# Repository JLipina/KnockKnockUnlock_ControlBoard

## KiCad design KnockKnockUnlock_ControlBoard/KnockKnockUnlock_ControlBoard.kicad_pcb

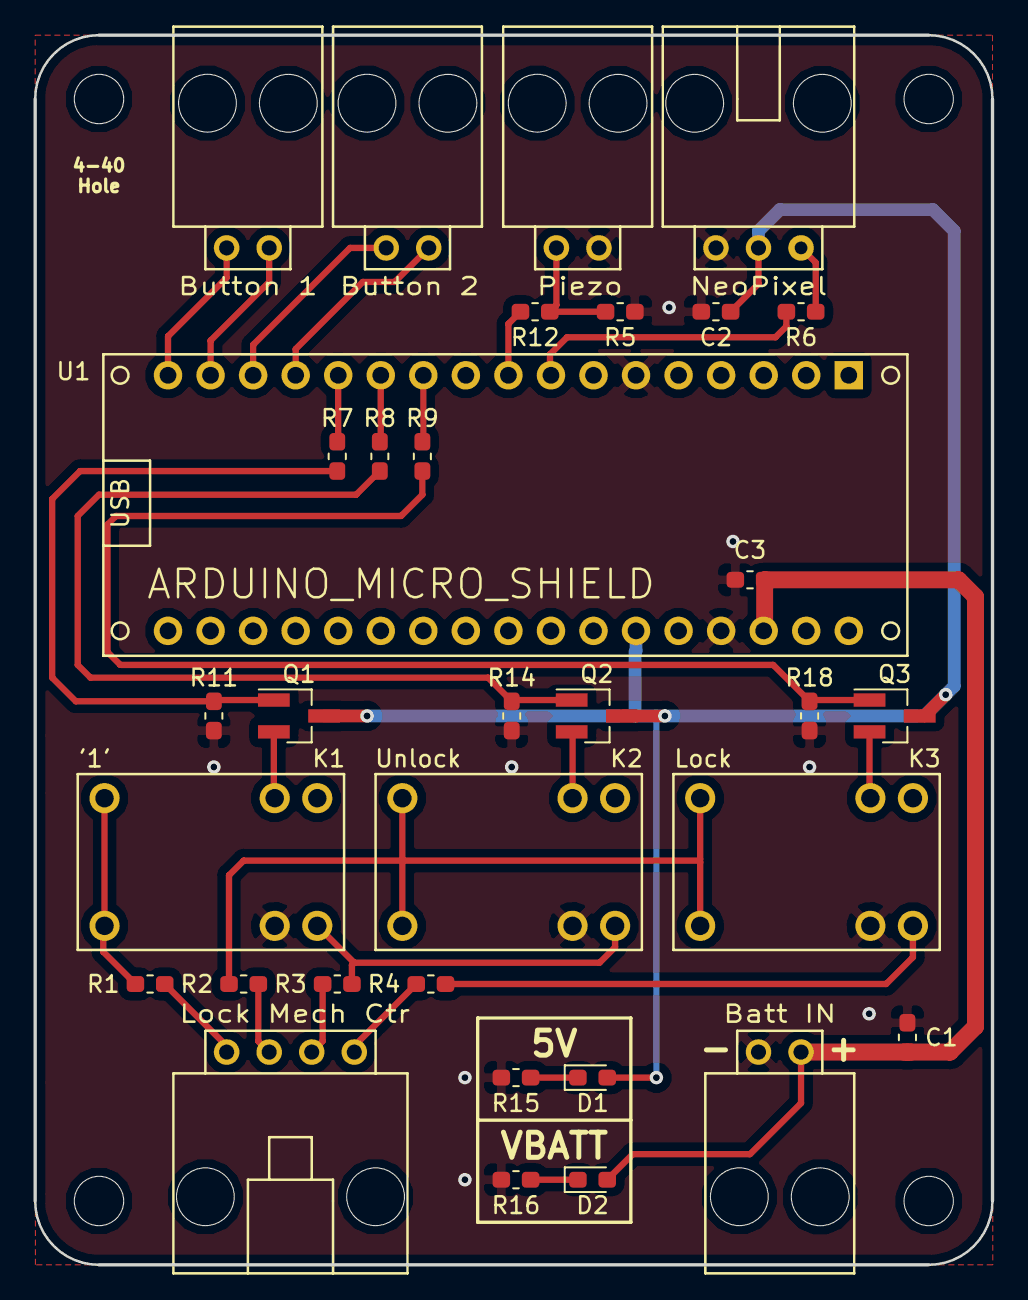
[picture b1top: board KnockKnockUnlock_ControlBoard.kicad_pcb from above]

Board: 2 copper layers, 57.2 x 73.4 mm, 33 parts (0 on the bottom side), 30 nets.

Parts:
C1, C2, C3: 10u; C_0603_1608Metric_Pad1.05x0.95mm_HandSolder
Conn1, Conn2, Conn5, Conn6: Molex_SL_02; MOLEX_SL_02_Horizontal
Conn3: Molex_SL_03; MOLEX_SL_03_Horizontal
Conn4: Molex_SL_04; MOLEX_SL_04_Horizontal
D1, D2: LED; LED_0603_1608Metric_Pad1.05x0.95mm_HandSolder
K1, K2, K3: HK4100F_5V_Relay
Q1, Q2, Q3: Q_NMOS_GSD; SOT-23_Handsoldering
R1, R2, R3, R4, R6, R7, R8, R9, R12: 0; R_0603_1608Metric_Pad1.05x0.95mm_HandSolder
R5: 10k; R_0603_1608Metric_Pad1.05x0.95mm_HandSolder
R11, R14, R18: 2.2M; R_0603_1608Metric_Pad1.05x0.95mm_HandSolder
R15, R16: 500; R_0603_1608Metric_Pad1.05x0.95mm_HandSolder
U1: ARDUINO_MICRO_SHIELD

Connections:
5V: C2.1, Conn3.2, D1.2, Q1.3, Q2.3, Q3.3, U1.5V
Button_1_Ctr: Q1.1, R7.2, R11.1
Button_1_IN: Conn5.1, U1.12
Button_1_OUT: Conn5.2, U1.11
Button_2_IN: Conn6.1, U1.10
Button_2_OUT: Conn6.2, U1.9
Button_Lock_Ctr: Q3.1, R9.2, R18.1
Button_Unlock_Ctr: Q2.1, R8.2, R14.1
GND: C1.2, C2.2, C3.1, Conn1.2, Conn2.2, Conn3.1, K1.C2, K2.C2, K3.C2, R5.2, R11.2, R14.2, R15.2, R16.2, R18.2, U1.GND
Lock_Mech_Pin1: K1.1, K1.2, R1.1
Lock_Mech_Pin4: K2.1, K2.2, K3.1, K3.2, R2.1
Lock_Mech_Pin5: K1.4, K2.4, R3.1
Lock_Mech_Pin7: K3.4, R4.1
NeoPixel_DIN: Conn3.3, R6.2
unnamed: Conn4.1, R4.2
unnamed: Conn4.2, R3.2
unnamed: Conn4.3, R2.2
unnamed: Conn4.4, R1.2
unnamed: D1.1, R15.1
unnamed: D2.1, R16.1
unnamed: K1.C1, Q1.2
unnamed: K2.C1, Q2.2
unnamed: K3.C1, Q3.2
unnamed: R6.1, U1.3
unnamed: R7.1, U1.8
unnamed: R8.1, U1.7
unnamed: R9.1, U1.6
unnamed: R12.1, U1.4
Piezo_Sensor: Conn2.1, R5.1, R12.2
VBATT: C1.1, C3.2, Conn1.1, D2.2, U1.VI

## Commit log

2019-09-25 Added gitignore
2019-09-25 Created KiCAD project
    Libraries mapped and preparing to create new symbols and footprints.
2019-09-25 Created Symbols and Footprints
2019-09-26 Schematic Finished
2019-09-26 Started Layout
    Changed FET pinout, mapped all symbols to footprints, generated netlist.
2019-09-26 All Components Placed
    Parts need finer positioning, then routing can be started.
2019-09-27 Routing Complete
    Silkecreen Complete. Schematic tweaked during process to allow for cleaner routing.
2019-10-06 Added Gerb Files
2019-10-13 Added Documentation
